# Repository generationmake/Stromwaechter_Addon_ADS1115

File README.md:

# Stromwaechter_Addon_ADS1115
Addon PCB for the Stromwaechter system with an ADS1115

## PCB

### Top

### Bottom

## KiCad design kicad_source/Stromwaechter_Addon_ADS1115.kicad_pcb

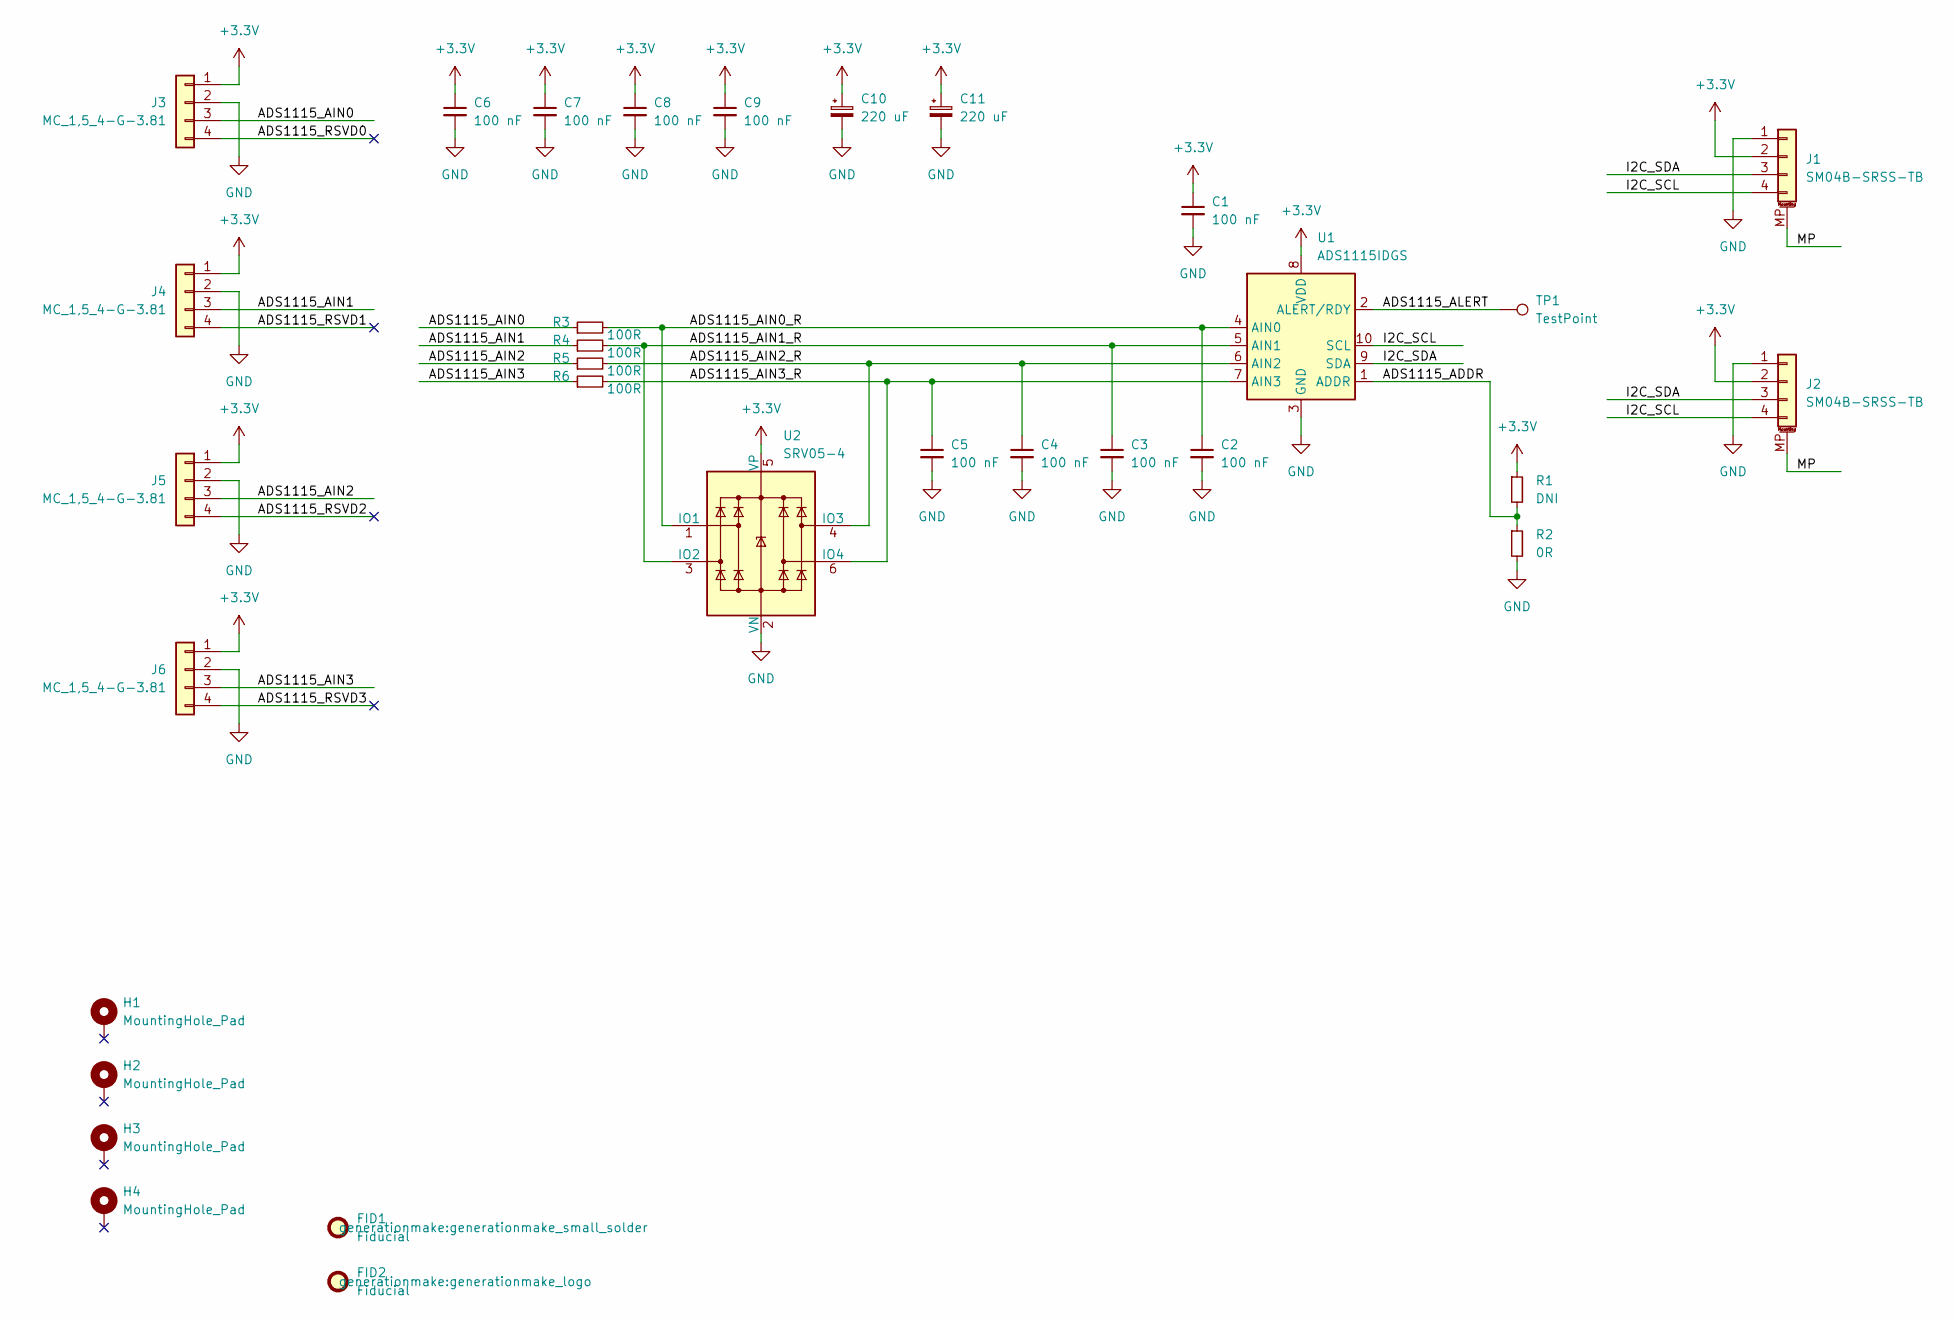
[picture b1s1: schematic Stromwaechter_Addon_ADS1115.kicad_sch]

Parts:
C1, C2, C3, C4, C5, C6, C7, C8, C9: 100 nF; C_0603_1608Metric
C10, C11: 220 uF; CP_Elec_6.3x9.9
FID1: Fiducial; generationmake_small_solder
FID2: Fiducial; generationmake_logo
H1, H2, H3, H4: MountingHole_Pad; MountingHole_3.2mm_M3_DIN965_Pad
J1, J2: SM04B-SRSS-TB; JST_SH_SM04B-SRSS-TB_1x04-1MP_P1.00mm_Horizontal
J3, J4, J5, J6: MC_1,5_4-G-3.81; PhoenixContact_MC_1,5_4-G-3.81_1x04_P3.81mm_Horizontal
R1: DNI; R_0603_1608Metric
R2: 0R; R_0603_1608Metric
R3, R4, R5, R6: 100R; R_0603_1608Metric
TP1: TestPoint; TestPoint_Pad_D1.5mm
U1: ADS1115IDGS; TSSOP-10_3x3mm_P0.5mm
U2: SRV05-4; SOT-23-6

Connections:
+3.3V: C1.1, C6.1, C7.1, C8.1, C9.1, C10.1, C11.1, J1.2, J2.2, J3.1, J4.1, J5.1, J6.1, R1.1, U1.8 (VDD), U2.5 (VP)
/ADS1115_ADDR: R1.2, R2.1, U1.1 (ADDR)
/ADS1115_AIN0: J3.3, R3.1
/ADS1115_AIN0_R: C2.1, R3.2, U1.4 (AIN0), U2.1 (IO1)
/ADS1115_AIN1: J4.3, R4.1
/ADS1115_AIN1_R: C3.1, R4.2, U1.5 (AIN1), U2.3 (IO2)
/ADS1115_AIN2: J5.3, R5.1
/ADS1115_AIN2_R: C4.1, R5.2, U1.6 (AIN2), U2.4 (IO3)
/ADS1115_AIN3: J6.3, R6.1
/ADS1115_AIN3_R: C5.1, R6.2, U1.7 (AIN3), U2.6 (IO4)
/ADS1115_ALERT: TP1.1, U1.2 (ALERT/RDY)
/ADS1115_RSVD0: J3.4
/ADS1115_RSVD1: J4.4
/ADS1115_RSVD2: J5.4
/ADS1115_RSVD3: J6.4
/I2C_SCL: J1.4, J2.4, U1.10 (SCL)
/I2C_SDA: J1.3, J2.3, U1.9 (SDA)
/MP: J1.MP (MountPin), J2.MP (MountPin)
GND: C1.2, C2.2, C3.2, C4.2, C5.2, C6.2, C7.2, C8.2, C9.2, C10.2, C11.2, J1.1, J2.1, J3.2, J4.2, J5.2, J6.2, R2.2, U1.3 (GND), U2.2 (VN)

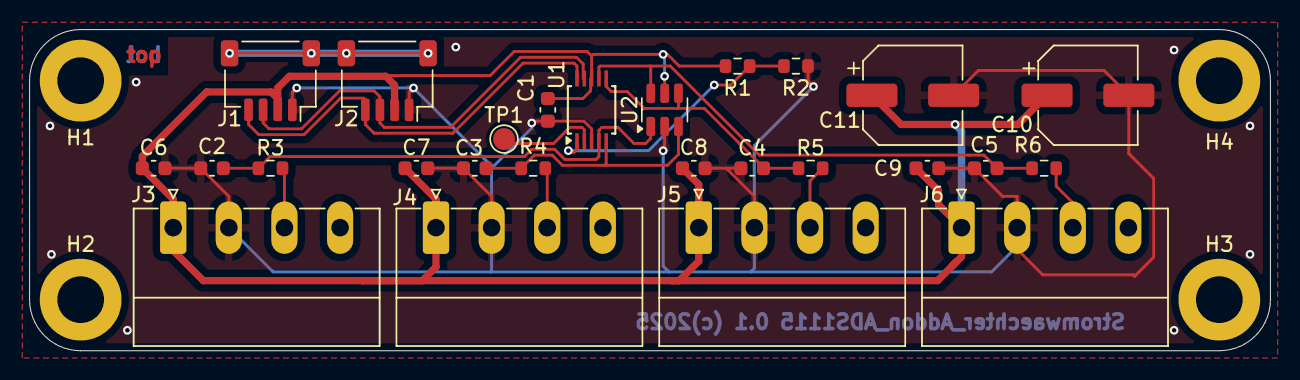
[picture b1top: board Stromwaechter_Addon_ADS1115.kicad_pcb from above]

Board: 2 copper layers, 85.0 x 22.0 mm, 32 parts (1 on the bottom side), 15 nets.

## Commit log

2025-09-03 started kicad poject
2025-09-04 generated layout, added mounting holes
2025-09-04 added schematic pdf
2025-09-07 added some capacitors on vcc and a testpoint at ads1115_alert
2025-09-07 added github workflow
2025-09-07 fixed spelling
2025-09-07 adjusted formatting checks
2025-09-07 updated pcb
2025-09-07 added labels, made DRC
2025-09-07 updated pdf schematic
2025-09-08 fixed DRC errors
2025-09-08 added images
2025-10-27 Bump actions/upload-artifact from 4 to 5
    Bumps [actions/upload-artifact](https://github.com/actions/upload-artifact) from 4 to 5.
    - [Release notes](https://github.com/actions/upload-artifact/releases)
    - [Commits](https://github.com/actions/upload-artifact/compare/v4...v5)
    ---
    updated-dependencies:
    - dependency-name: actions/upload-artifact
2025-10-27 Bump actions/download-artifact from 5 to 6
    Bumps [actions/download-artifact](https://github.com/actions/download-artifact) from 5 to 6.
    - [Release notes](https://github.com/actions/download-artifact/releases)
    - [Commits](https://github.com/actions/download-artifact/compare/v5...v6)
    ---
    updated-dependencies:
    - dependency-name: actions/download-artifact
2025-11-21 Bump actions/checkout from 5 to 6
    Bumps [actions/checkout](https://github.com/actions/checkout) from 5 to 6.
    - [Release notes](https://github.com/actions/checkout/releases)
    - [Changelog](https://github.com/actions/checkout/blob/main/CHANGELOG.md)
    - [Commits](https://github.com/actions/checkout/compare/v5...v6)
    ---
    updated-dependencies:
2025-12-15 Bump actions/download-artifact from 5 to 7
    Bumps [actions/download-artifact](https://github.com/actions/download-artifact) from 5 to 7.
    - [Release notes](https://github.com/actions/download-artifact/releases)
    - [Commits](https://github.com/actions/download-artifact/compare/v5...v7)
    ---
    updated-dependencies:
    - dependency-name: actions/download-artifact
2025-12-15 Bump actions/upload-artifact from 4 to 6
    Bumps [actions/upload-artifact](https://github.com/actions/upload-artifact) from 4 to 6.
    - [Release notes](https://github.com/actions/upload-artifact/releases)
    - [Commits](https://github.com/actions/upload-artifact/compare/v4...v6)
    ---
    updated-dependencies:
    - dependency-name: actions/upload-artifact

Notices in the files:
kicad_source/Stromwaechter_Addon_ADS1115.kicad_pcb:
Stromwaechter_Addon_ADS1115 0.1 (c)2025
